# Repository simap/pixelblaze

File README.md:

# Pixelblaze

This repo includes open source information related to [Pixelblaze](https://electromage.com/pixelblaze).

* [Pattern code Reference](README.expressions.md)
* [Mapper code Reference](README.mapper.md)

**Setup, Guides and Documentation:** https://electromage.com/docs

Community:

* [Forums](https://forum.electromage.com/)
* [Patterns](https://electromage.com/patterns/)

Pixelblaze itself isn't open source, though many of its components and add-on/expansions are:

* [https://github.com/simap/Apa102Adapter](https://github.com/simap/Apa102Adapter)
* [https://github.com/simap/Ws2812Adapter](https://github.com/simap/Ws2812Adapter)
* [https://github.com/simap/Ws2801Adapter](https://github.com/simap/Ws2801Adapter)
* [https://github.com/simap/PBDriverAdapter](https://github.com/simap/PBDriverAdapter)
* [https://github.com/simap/Arduino_fixpt](https://github.com/simap/Arduino_fixpt)
* [https://github.com/simap/WiFiManager](https://github.com/simap/WiFiManager)
* [https://github.com/simap/Time](https://github.com/simap/Time)
* [Output Expander / Serial 8 Channel WS2812/APA102 Driver](https://github.com/simap/pixelblaze_output_expander)
* [Sensor Expansion Board](https://github.com/simap/pixelblaze_sensor_board)

Pixelblaze Related GitHub Projects:

* [https://github.com/simap/pixelblaze websocket example](https://github.com/simap/pixelblaze_websocket_example)
* [Discovery Service](http://discover.electromage.com/)
* [https://github.com/simap/Firestorm](https://github.com/simap/Firestorm)
* [https://github.com/simap/PixelblazeSensorBoardLibrary](https://github.com/simap/PixelblazeSensorBoardLibrary) (for Arduino)
* [https://github.com/simap/flower_chandelier](https://github.com/simap/flower_chandelier)
* [PixelTeleporter](https://github.com/zranger1/PixelTeleporter) - Virtual LEDs for previewing 2D/3D patterns on a computer
* [https://github.com/zranger1/PixelblazePatterns](https://github.com/zranger1/PixelblazePatterns) - Multisegment and other pattern tools
* [https://github.com/Roger-random/glowflow](https://github.com/Roger-random/glowflow) - Interactive light sculpture filled with virtual liquid
* [https://github.com/alejandrosame/pixelblaze-animations](https://github.com/alejandrosame/pixelblaze-animations) Patterns and pure-browser emulation with visualizers 
* [https://github.com/zranger1/expander-universe](https://github.com/zranger1/expander-universe) Lets you drive addressable LEDs with your computer, a USB->Serial adapter in Processing
* [https://github.com/derwentx/js-pixelblaze-expander](https://github.com/derwentx/js-pixelblaze-expander) A NodeJS Library for controlling the Output Expander / Serial to 8x LED Drivers
* [https://github.com/bosporos/libpbx](https://github.com/bosporos/libpbx) A C library for controlling the Output Expander / Serial to 8x LED Drivers
* [https://github.com/zranger1/hubitatpixelblazedriver](https://github.com/zranger1/hubitatpixelblazedriver) Hubitat Elevation device handler for the Pixelblaze
* [https://github.com/zranger1/pixelblaze-client](https://github.com/zranger1/pixelblaze-client) Pixelblaze client library for Python by ZRanger1
* [https://github.com/NickWaterton/Pixelblaze-Async](https://github.com/NickWaterton/Pixelblaze-Async) Async Pixelblaze client library for Python by NickWaterton 

Additional Licenses:

* [ArduinoJson](https://github.com/bblanchon/ArduinoJson/blob/5.x/LICENSE.md)
* [AsyncTCP](https://github.com/me-no-dev/AsyncTCP/blob/master/LICENSE)
* [Time](https://github.com/simap/Time/blob/master/Time.cpp#L5)
* [Arduino Websockets](https://github.com/simap/arduinoWebSockets/blob/master/LICENSE)
* [micro-ecc](https://github.com/kmackay/micro-ecc/blob/master/LICENSE.txt)
* [ESPAsyncWebServer](https://github.com/me-no-dev/ESPAsyncWebServer/blob/master/src/WebServer.cpp#L4)
* [jQuery](https://jquery.org/license/)
* [underscore](https://github.com/jashkenas/underscore/blob/master/LICENSE)
* [Bootstrap](https://github.com/twbs/bootstrap/blob/master/LICENSE)
* [FileSaver.js](https://github.com/eligrey/FileSaver.js/blob/master/LICENSE.md)
* [lz-string](https://github.com/pieroxy/lz-string/blob/master/LICENSE)
* [mdn-webgl](https://github.com/gregtatum/mdn-webgl/blob/master/LICENSE)
* [Pickr](https://github.com/Simonwep/pickr/blob/master/LICENSE)
* [Ace](https://github.com/ajaxorg/ace/blob/master/LICENSE)
* [Esprima](https://github.com/jquery/esprima/blob/master/LICENSE.BSD)
* [lodash](https://github.com/lodash/lodash/blob/master/LICENSE)

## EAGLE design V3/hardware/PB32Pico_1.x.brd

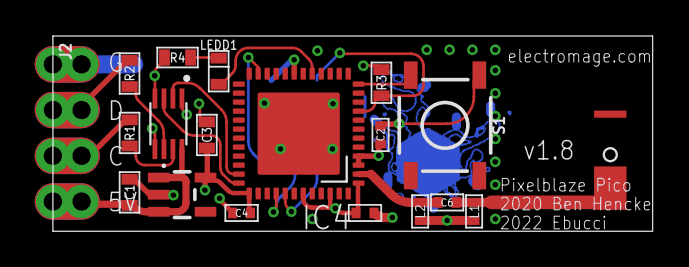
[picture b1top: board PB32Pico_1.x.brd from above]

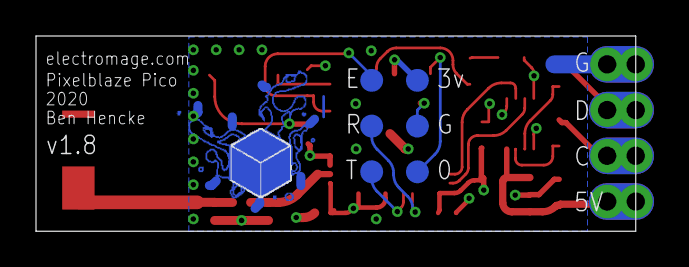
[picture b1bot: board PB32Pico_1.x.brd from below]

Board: 4 copper layers, 33.3 x 10.8 mm, 27 parts (7 on the bottom side), 18 nets.

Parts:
C1: 1.0uF; C0603
C2, C4, C5: 0.1uF; C0402
C3: 10uF; C0603
C6: 1.6PF; C0402
IC2: SN74LVC2T45DCUR; SOP50P310X90-8N
IC3: 3.3V; SOT23-5
IC4: ESP32-PICO-D4UM-ESP32-PICO-D4; PICO-D4-QFN48
J1, J2: 1X04_NO_SILK
L1, L2: L-0402; L0402
LEDD1: LED-0603; LED0603
R1, R2, R4: 100; R0603
R3: 10k; R0603
S1: MOMENTARY-SWITCH-SPST-SMD-5.2MM; TACTILE_SWITCH_SMD_5.2MM
TP1, TP2, TP3, TP4, TP5, TP6: TEST-POINT3X5; PAD.03X.05
U$2: CHIP-ANTENNASHORT; CHIPANTENNA-1206-SHORT
U$3: ELECTRO_MAGE_PCB4_PIXEL_2#PNG

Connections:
+3V3: C2.1, C3.1, C4.1, C5.1, IC2.1, IC2.5, IC3.5, IC4.1, IC4.3, IC4.4, IC4.19, IC4.37, IC4.43, IC4.46, R3.1, TP5.P$1
+5V: C1.1, IC2.8, IC3.1, IC3.3, J1.4, J2.4
BUTTON: IC4.12, S1.3
EN: IC4.9, R3.2, TP3.P$1
GND: C1.2, C2.2, C3.2, C4.2, C5.2, IC2.4, IC3.2, IC4.EXP, J1.1, J2.1, L1.2, L2.2, R4.1, S1.1, TP6.P$1
IO0: IC4.23, TP4.P$1
unnamed: C6.1, L1.1, U$2.P$1
unnamed: IC4.17, LEDD1.A
unnamed: LEDD1.C, R4.2
unnamed: IC2.7, R1.1
unnamed: IC2.6, R2.1
unnamed: C6.2, IC4.2, L2.1
SCK: IC2.2, IC4.35
SCK_OUT: J1.3, J2.3, R1.2
SDO: IC2.3, IC4.36
SDO_OUT: J1.2, J2.2, R2.2
U0TX: IC4.41, TP2.P$1
UORX: IC4.40, TP1.P$1

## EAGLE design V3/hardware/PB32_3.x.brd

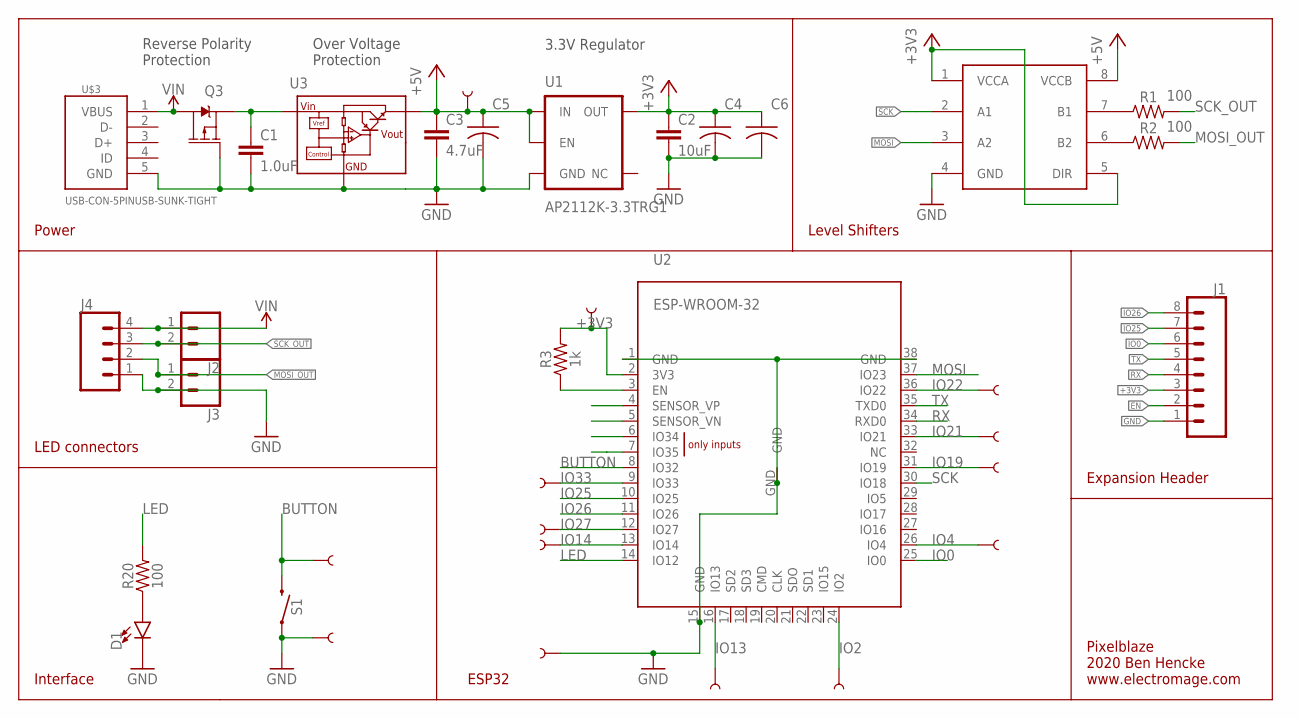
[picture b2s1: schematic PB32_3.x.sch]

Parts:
C1: 1.0uF; 0805-CAP
C2: 10uF; 0805
C3: 4.7uF; 0603
C4, C5, C6: 0.1uF; C0402K
D1: LED0603; LED-0603
GP1, GP3, GP6, GP8, GP9: SMTPAD; PAD
IO2, IO4, IO13, IO14, IO19, IO21, IO22, IO27, IO33: SMTPAD; PAD
J1: CONN_08LOCK; 1X08_LOCK
J2, J3: CONN_025MM; SCREWTERMINAL-5MM-2
J4: CONN_041X04_NO_SILK; 1X04_NO_SILK
Q3: 2.5A/30V/105mΩ; SOT23-3
R1, R2, R20: 100; 0603
R3: 1k; 0603
S1: MOMENTARY-SWITCH-SPST-SMD-5.2MM; TACTILE_SWITCH_SMD_5.2MM
U1: AP2112K-3.3TRG1; SOT23-5
U2: ESP-WROOM-32
U3: NX1117C15Z; SOT223
U$1: SN74LVC2T45DCUR; SOP50P310X90-8N
U$3: USB-CON-5PINUSB-SUNK-TIGHT; USB-SUNK-TIGHT

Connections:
+3V3: C2.1, C4.1, C6.1, GP1.P$1, J1.3, R3.2, U1.5 (OUT), U2.2 (3V3), U$1.1 (VCCA), U$1.5 (DIR)
+5V: C3.1, C5.1, GP6.P$1, U1.1 (IN), U1.3 (EN), U3.2 (VOUT), U3.4 (VOUT), U$1.8 (VCCB)
BUTTON: GP8.P$1, S1.3 (2), U2.8 (IO32)
EN: J1.2, R3.1, U2.3 (EN)
GND: C1.2, C2.2, C3.2, C4.2, C5.2, C6.2, D1.C, GP3.P$1, GP9.P$1, J1.1, J3.2, J4.1, Q3.1 (G), S1.1, U1.2 (GND), U2.1 (GND), U2.15 (GND), U2.38 (GND), U2.GND, U3.1 (GND), U$1.4 (GND), U$3.5 (GND)
IO0: J1.6, U2.25 (IO0)
IO2: IO2.P$1, U2.24 (IO2)
IO4: IO4.P$1, U2.26 (IO4)
IO13: IO13.P$1, U2.16 (IO13)
IO14: IO14.P$1, U2.13 (IO14)
IO19: IO19.P$1, U2.31 (IO19)
IO21: IO21.P$1, U2.33 (IO21)
IO22: IO22.P$1, U2.36 (IO22)
IO25: J1.7, U2.10 (IO25)
IO26: J1.8, U2.11 (IO26)
IO27: IO27.P$1, U2.12 (IO27)
IO33: IO33.P$1, U2.9 (IO33)
LED: R20.2, U2.14 (IO12)
MOSI: U2.37 (IO23), U$1.3 (A2)
MOSI_OUT: J3.1, J4.2, R2.2
unnamed: C1.1, Q3.2 (S), U3.3 (VIN)
unnamed: R1.1, U$1.7 (B1)
unnamed: R2.1, U$1.6 (B2)
unnamed: D1.A, R20.1
RX: J1.4, U2.34 (RXD0)
SCK: U2.30 (IO18), U$1.2 (A1)
SCK_OUT: J2.2, J4.3, R1.2
TX: J1.5, U2.35 (TXD0)
VIN: J2.1, J4.4, Q3.3 (D), U$3.1 (VBUS)

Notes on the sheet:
Power
LED connectors
ESP32
Expansion Header
Level Shifters
Pixelblaze 2020 Ben Hencke www.electromage.com
Interface
Reverse Polarity Protection
Over Voltage Protection
3.3V Regulator

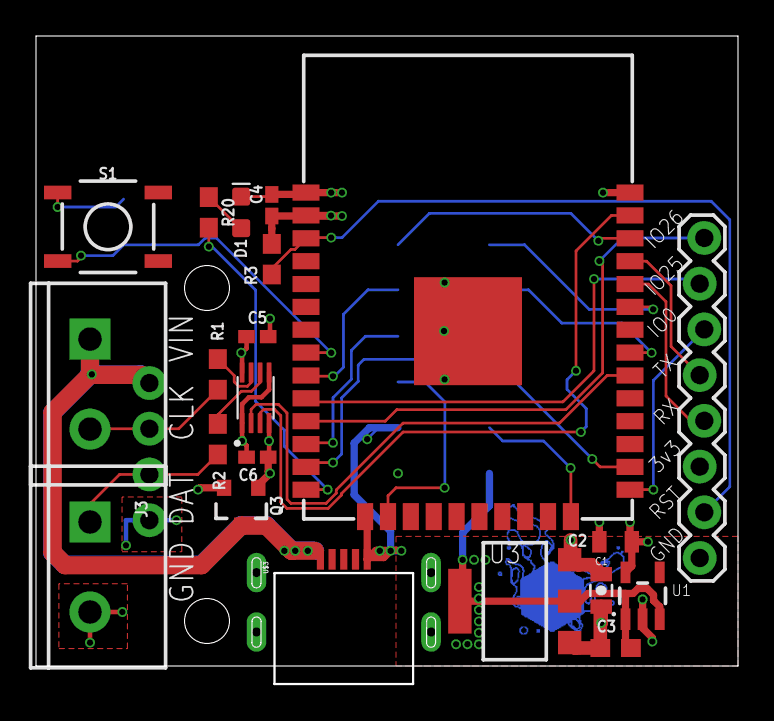
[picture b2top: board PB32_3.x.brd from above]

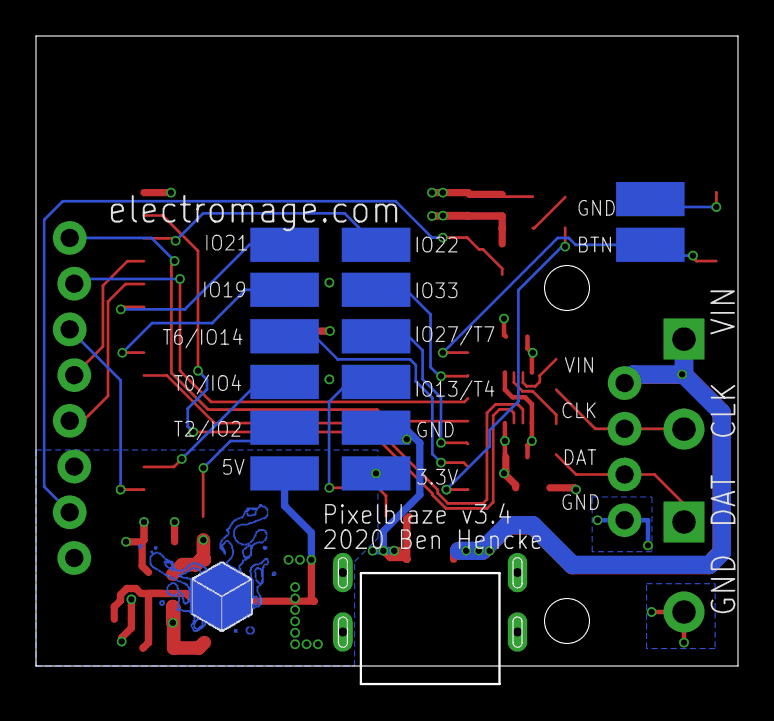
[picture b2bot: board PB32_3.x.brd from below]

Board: 4 copper layers, 38.9 x 35.9 mm, 37 parts (15 on the bottom side), 29 nets.

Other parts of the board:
U$2: ELECTRO_MAGE_PCB4_PIXEL_2#PNG

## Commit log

2017-08-05 docs and things
2018-01-20 updated docs for v2
2018-01-20 update for v2
2018-08-31 expansion board docs (oops!)
2018-08-31 add mapper docs
2019-04-14 First draft of troubleshooting guide
2019-04-14 Power, Log, Bootloader
2019-04-14 Computer USB power test
2019-04-15 Add illustrative images
2019-07-01 Restore missing 'z' from render3D example
2019-07-10 Fix minor typos
2019-07-10 Standardize on LF, remove CR+LF
2019-09-20 update for esp32
2019-09-20 clock/time functions
2019-12-14 update docs with info about watcher and controls and other small updates
2020-02-11 v2+ schematic (oops)
2020-03-06 was missing bitwise and/or
2020-03-06 arg to sqrt should be v
2020-08-20 bit about var scope
2020-08-20 fix toc and a few small improvements
2020-08-20 more about vars
2020-10-01 ignore
2020-10-02 reorganize, add tons more links
2020-10-02 more links, licenses, formatting
2020-10-02 hardware design files and pdf schematics
2020-10-05 license for v3 hw files
2020-10-26 another link
2020-12-31 docs!
    add docs for new math and array functions. expand docs on existing
    functions. spellcheck.
2021-01-13 guides, minor tweaks to expressions doc
    add quick start guides and some photos
    remove duplicate time/clock fn doc section
    fix toc link
2021-01-20 spelling
2021-02-08 more guides/docs
2021-04-06 Update README.md
    Add link for setup
2021-06-24 interface updates
2021-06-24 coordinate transformation api
2021-07-07 Update getting_started.md
    rel paths
2021-07-09 fix filenames and case
2021-09-14 Update README.md
    add python client refs
2021-09-26 Add guide: Intro to mapping
2021-09-28 Add guide: Websocket API
2021-10-08 add arrayReplace docs
2021-10-08 array literals now supported
2021-10-25 add link to ExpanderUniverse
2022-01-06 Improved explanation of USB power source w/12V supply.
2022-02-04 ignore more files
2022-02-04 image formatting
2022-02-04 update images
2022-02-04 remove spaces from filename
2022-02-04 update recommendations around the BI bin and mention the 12v expander
2022-02-04 no either
2022-04-23 PICO pcb reworked
2022-07-08 Updating with 3.24 changes - more ui controls and more!
2022-09-08 Fix Table of Contents links
2022-09-29 add palette api, small fixes
2022-10-02 new apis
2022-12-10 add links to reference docs
2023-01-19 Move guides to electromage.com
2023-03-31 perlin, pnrg, nodeId
2023-04-10 rework mapper docs
2023-04-10 doc example generator fn
2023-10-30 sequencer APIs
2023-10-30 remove v2 references, v3 only. fix typos, wording.
2023-11-08 PB+SB underneath enclosure
2024-04-23 Add Pixelblaze case files
2024-06-04 Add Fusion models for each variant

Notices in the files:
parts and their libraries:
SparkFun-Connectors: Licensing: Creative Commons ShareAlike 4.0 International - https://creativecommons.org/licenses/by-sa/4.0
NXP_60_26022015: This library may be distributed and adapted freely for any purpose, as long as NXP is credited and any new creation is licensed under the same terms.
